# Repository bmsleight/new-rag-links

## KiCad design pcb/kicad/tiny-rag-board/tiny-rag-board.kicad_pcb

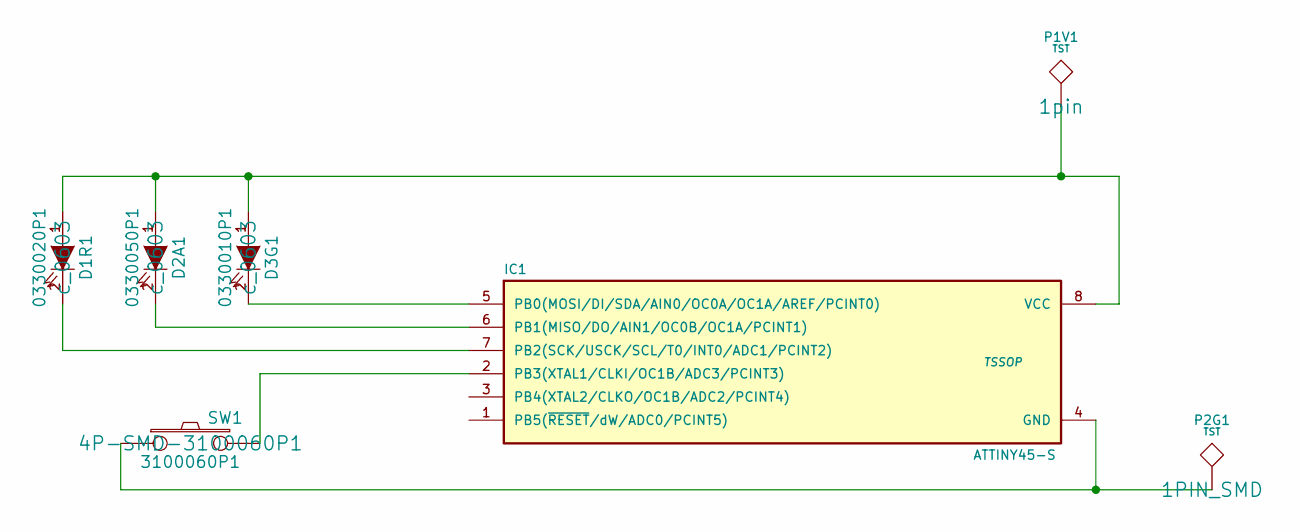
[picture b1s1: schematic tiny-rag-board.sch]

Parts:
D1R1: 0330020P1; c_0603
D2A1: 0330050P1; c_0603
D3G1: 0330010P1; c_0603
IC1: ATTINY45-S; TSSOP
P1V1: TST; 1pin
P2G1: TST; 1PIN_SMD
SW1: 3100060P1; 4P-SMD-3100060P1

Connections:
unnamed: D2A1.2 (K), IC1.6 (PB1(MISO/DO/AIN1/OC0B/OC1A/PCINT1))
unnamed: D3G1.2 (K), IC1.5 (PB0(MOSI/DI/SDA/AIN0/OC0A/OC1A/AREF/PCI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)
unnamed: IC1.2 (PB3(XTAL1/CLKI/OC1B/ADC3/PCINT3)), SW1.2
unnamed: IC1.4 (GND), P2G1.1, SW1.1
unnamed: D1R1.2 (K), IC1.7 (PB2(SCK/USCK/SCL/T0/INT0/ADC1/PCINT2))
unnamed: D1R1.1 (A), D2A1.1 (A), D3G1.1 (A), IC1.8 (VCC), P1V1.1

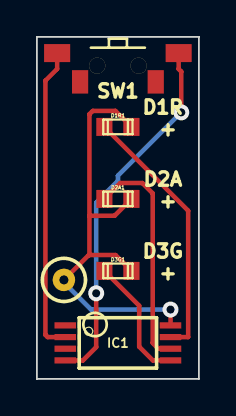
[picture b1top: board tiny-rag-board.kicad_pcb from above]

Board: 2 copper layers, 9.0 x 19.0 mm, 7 parts (1 on the bottom side), 6 nets.

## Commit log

2014-07-26 First push
2014-07-28 pcb order
2014-07-28 2014-07-28 Order Confirmation No: 125753
2014-08-21 Update to structure
2014-08-31 Adding Button
2014-09-01 New sized - pcb front entry adnd printer setting
2014-09-01 New end of cufflink
2014-09-06 New style (should fork really)
2014-09-07 Adding bars to stoip inter visability
2014-09-07 New config - blue printer is cooler, pink is hot
